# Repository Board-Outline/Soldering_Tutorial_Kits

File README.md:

# Soldering_Tutorial_Kits

The Soldering Tutorial Kits boards are designed to help people learn to solder SMD components with lots of repetition and a fair quantity of cheap and available parts. Their goal is to give one the confidence and skills needed to work on more demanding professional or hobby projects.

Those parts will be used as a part of an Beginner SMD Tutorial Corse. 

# License

The project is released under the [Creative Commons Attribution-ShareAlike 4.0 International (CC BY-SA 4.0)](https://creativecommons.org/licenses/by-sa/4.0/).

Note: This is a human-readable summary of (and not a substitute for) the [license](https://creativecommons.org/licenses/by-sa/4.0/legalcode).

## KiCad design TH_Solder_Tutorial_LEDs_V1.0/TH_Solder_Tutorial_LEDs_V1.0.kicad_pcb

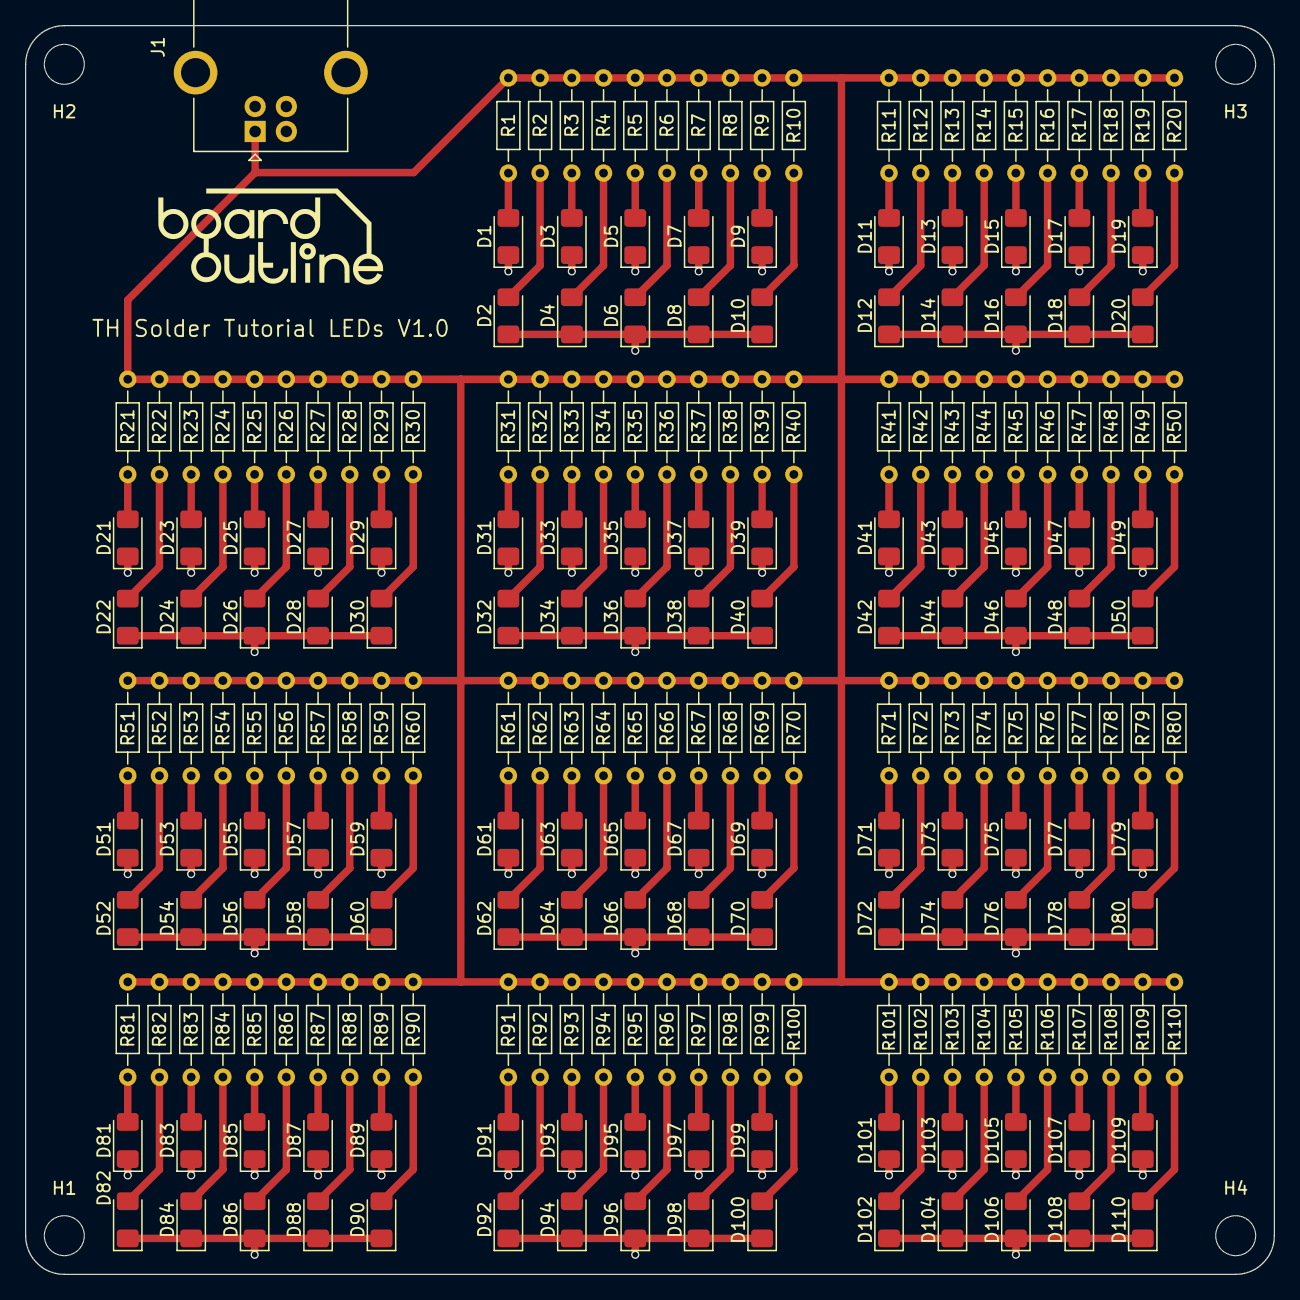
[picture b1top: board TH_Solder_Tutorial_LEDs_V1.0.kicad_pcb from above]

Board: 2 copper layers, 100.0 x 100.0 mm, 225 parts (0 on the bottom side), 112 nets.

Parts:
D1, D2, D3, D4, D5, D6, D7, D8, D9, D10, D11, D12, D13, D14, D15, D16, D17, D18, D19, D20, D21, D22, D23, D24, D25, D26, D27, D28, D29, D30, D31, D32, D33, D34, D35, D36, D37, D38, D39, D40, D41, D42, D43, D44, D45, D46, D47, D48, D49, D50, D51, D52, D53, D54, D55, D56, D57, D58, D59, D60, D61, D62, D63, D64, D65, D66, D67, D68, D69, D70, D71, D72, D73, D74, D75, D76, D77, D78, D79, D80, D81, D82, D83, D84, D85, D86, D87, D88, D89, D90, D91, D92, D93, D94, D95, D96, D97, D98, D99, D100, D101, D102, D103, D104, D105, D106, D107, D108, D109, D110: LED; LED_1206_3216Metric_Pad1.42x1.75mm_HandSolder
H1, H2, H3, H4: MountingHole; MountingHole_3.2mm_M3_DIN965
J1: USB_B; USB_B_OST_USB-B1HSxx_Horizontal
R1, R2, R3, R4, R5, R6, R7, R8, R9, R10, R11, R12, R13, R14, R15, R16, R17, R18, R19, R20, R21, R22, R23, R24, R25, R26, R27, R28, R29, R30, R31, R32, R33, R34, R35, R36, R37, R38, R39, R40, R41, R42, R43, R44, R45, R46, R47, R48, R49, R50, R51, R52, R53, R54, R55, R56, R57, R58, R59, R60, R61, R62, R63, R64, R65, R66, R67, R68, R69, R70, R71, R72, R73, R74, R75, R76, R77, R78, R79, R80, R81, R82, R83, R84, R85, R86, R87, R88, R89, R90, R91, R92, R93, R94, R95, R96, R97, R98, R99, R100, R101, R102, R103, R104, R105, R106, R107, R108, R109, R110: 220R; R_Axial_DIN0204_L3.6mm_D1.6mm_P7.62mm_Horizontal

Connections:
+5V: J1.1 (VBUS), R1.1, R2.1, R3.1, R4.1, R5.1, R6.1, R7.1, R8.1, R9.1, R10.1, R11.1, R12.1, R13.1, R14.1, R15.1, R16.1, R17.1, R18.1, R19.1, R20.1, R21.1, R22.1, R23.1, R24.1, R25.1, R26.1, R27.1, R28.1, R29.1, R30.1, R31.1, R32.1, R33.1, R34.1, R35.1, R36.1, R37.1, R38.1, R39.1, R40.1, R41.1, R42.1, R43.1, R44.1, R45.1, R46.1, R47.1, R48.1, R49.1, R50.1, R51.1, R52.1, R53.1, R54.1, R55.1, R56.1, R57.1, R58.1, R59.1, R60.1, R61.1, R62.1, R63.1, R64.1, R65.1, R66.1, R67.1, R68.1, R69.1, R70.1, R71.1, R72.1, R73.1, R74.1, R75.1, R76.1, R77.1, R78.1, R79.1, R80.1, R81.1, R82.1, R83.1, R84.1, R85.1, R86.1, R87.1, R88.1, R89.1, R90.1, R91.1, R92.1, R93.1, R94.1, R95.1, R96.1, R97.1, R98.1, R99.1, R100.1, R101.1, R102.1, R103.1, R104.1, R105.1, R106.1, R107.1, R108.1, R109.1, R110.1
GND: D1.1 (K), D2.1 (K), D3.1 (K), D4.1 (K), D5.1 (K), D6.1 (K), D7.1 (K), D8.1 (K), D9.1 (K), D10.1 (K), D11.1 (K), D12.1 (K), D13.1 (K), D14.1 (K), D15.1 (K), D16.1 (K), D17.1 (K), D18.1 (K), D19.1 (K), D20.1 (K), D21.1 (K), D22.1 (K), D23.1 (K), D24.1 (K), D25.1 (K), D26.1 (K), D27.1 (K), D28.1 (K), D29.1 (K), D30.1 (K), D31.1 (K), D32.1 (K), D33.1 (K), D34.1 (K), D35.1 (K), D36.1 (K), D37.1 (K), D38.1 (K), D39.1 (K), D40.1 (K), D41.1 (K), D42.1 (K), D43.1 (K), D44.1 (K), D45.1 (K), D46.1 (K), D47.1 (K), D48.1 (K), D49.1 (K), D50.1 (K), D51.1 (K), D52.1 (K), D53.1 (K), D54.1 (K), D55.1 (K), D56.1 (K), D57.1 (K), D58.1 (K), D59.1 (K), D60.1 (K), D61.1 (K), D62.1 (K), D63.1 (K), D64.1 (K), D65.1 (K), D66.1 (K), D67.1 (K), D68.1 (K), D69.1 (K), D70.1 (K), D71.1 (K), D72.1 (K), D73.1 (K), D74.1 (K), D75.1 (K), D76.1 (K), D77.1 (K), D78.1 (K), D79.1 (K), D80.1 (K), D81.1 (K), D82.1 (K), D83.1 (K), D84.1 (K), D85.1 (K), D86.1 (K), D87.1 (K), D88.1 (K), D89.1 (K), D90.1 (K), D91.1 (K), D92.1 (K), D93.1 (K), D94.1 (K), D95.1 (K), D96.1 (K), D97.1 (K), D98.1 (K), D99.1 (K), D100.1 (K), D101.1 (K), D102.1 (K), D103.1 (K), D104.1 (K), D105.1 (K), D106.1 (K), D107.1 (K), D108.1 (K), D109.1 (K), D110.1 (K), J1.4 (GND), J1.5 (Shield)
unnamed: D1.2 (A), R1.2
unnamed: D2.2 (A), R2.2
unnamed: D3.2 (A), R3.2
unnamed: D4.2 (A), R4.2
unnamed: D5.2 (A), R5.2
unnamed: D6.2 (A), R6.2
unnamed: D7.2 (A), R7.2
unnamed: D8.2 (A), R8.2
unnamed: D9.2 (A), R9.2
unnamed: D10.2 (A), R10.2
unnamed: D11.2 (A), R11.2
unnamed: D12.2 (A), R12.2
unnamed: D13.2 (A), R13.2
unnamed: D14.2 (A), R14.2
unnamed: D15.2 (A), R15.2
unnamed: D16.2 (A), R16.2
unnamed: D17.2 (A), R17.2
unnamed: D18.2 (A), R18.2
unnamed: D19.2 (A), R19.2
unnamed: D20.2 (A), R20.2
unnamed: D21.2 (A), R21.2
unnamed: D22.2 (A), R22.2
unnamed: D23.2 (A), R23.2
unnamed: D24.2 (A), R24.2
unnamed: D25.2 (A), R25.2
unnamed: D26.2 (A), R26.2
unnamed: D27.2 (A), R27.2
unnamed: D28.2 (A), R28.2
unnamed: D29.2 (A), R29.2
unnamed: D30.2 (A), R30.2
unnamed: D31.2 (A), R31.2
unnamed: D32.2 (A), R32.2
unnamed: D33.2 (A), R33.2
unnamed: D34.2 (A), R34.2
unnamed: D35.2 (A), R35.2
unnamed: D36.2 (A), R36.2
unnamed: D37.2 (A), R37.2
unnamed: D38.2 (A), R38.2
unnamed: D39.2 (A), R39.2
unnamed: D40.2 (A), R40.2
unnamed: D41.2 (A), R41.2
unnamed: D42.2 (A), R42.2
unnamed: D43.2 (A), R43.2
unnamed: D44.2 (A), R44.2
unnamed: D45.2 (A), R45.2
unnamed: D46.2 (A), R46.2
unnamed: D47.2 (A), R47.2
unnamed: D48.2 (A), R48.2
unnamed: D49.2 (A), R49.2
unnamed: D50.2 (A), R50.2
unnamed: D51.2 (A), R51.2
unnamed: D52.2 (A), R52.2
unnamed: D53.2 (A), R53.2
unnamed: D54.2 (A), R54.2
unnamed: D55.2 (A), R55.2
unnamed: D56.2 (A), R56.2
unnamed: D57.2 (A), R57.2
unnamed: D58.2 (A), R58.2
unnamed: D59.2 (A), R59.2
unnamed: D60.2 (A), R60.2
unnamed: D61.2 (A), R61.2
unnamed: D62.2 (A), R62.2
unnamed: D63.2 (A), R63.2
unnamed: D64.2 (A), R64.2
unnamed: D65.2 (A), R65.2
unnamed: D66.2 (A), R66.2
unnamed: D67.2 (A), R67.2
unnamed: D68.2 (A), R68.2
unnamed: D69.2 (A), R69.2
unnamed: D70.2 (A), R70.2
unnamed: D71.2 (A), R71.2
unnamed: D72.2 (A), R72.2
unnamed: D73.2 (A), R73.2
unnamed: D74.2 (A), R74.2
unnamed: D75.2 (A), R75.2
unnamed: D76.2 (A), R76.2
unnamed: D77.2 (A), R77.2
unnamed: D78.2 (A), R78.2
unnamed: D79.2 (A), R79.2
unnamed: D80.2 (A), R80.2
unnamed: D81.2 (A), R81.2
unnamed: D82.2 (A), R82.2
unnamed: D83.2 (A), R83.2
unnamed: D84.2 (A), R84.2
unnamed: D85.2 (A), R85.2
unnamed: D86.2 (A), R86.2
unnamed: D87.2 (A), R87.2
unnamed: D88.2 (A), R88.2
unnamed: D89.2 (A), R89.2
unnamed: D90.2 (A), R90.2
unnamed: D91.2 (A), R91.2
unnamed: D92.2 (A), R92.2
unnamed: D93.2 (A), R93.2
unnamed: D94.2 (A), R94.2
unnamed: D95.2 (A), R95.2
unnamed: D96.2 (A), R96.2
unnamed: D97.2 (A), R97.2
unnamed: D98.2 (A), R98.2
unnamed: D99.2 (A), R99.2
unnamed: D100.2 (A), R100.2
unnamed: D101.2 (A), R101.2
unnamed: D102.2 (A), R102.2
unnamed: D103.2 (A), R103.2
unnamed: D104.2 (A), R104.2
unnamed: D105.2 (A), R105.2
unnamed: D106.2 (A), R106.2
unnamed: D107.2 (A), R107.2
unnamed: D108.2 (A), R108.2
unnamed: D109.2 (A), R109.2
unnamed: D110.2 (A), R110.2
